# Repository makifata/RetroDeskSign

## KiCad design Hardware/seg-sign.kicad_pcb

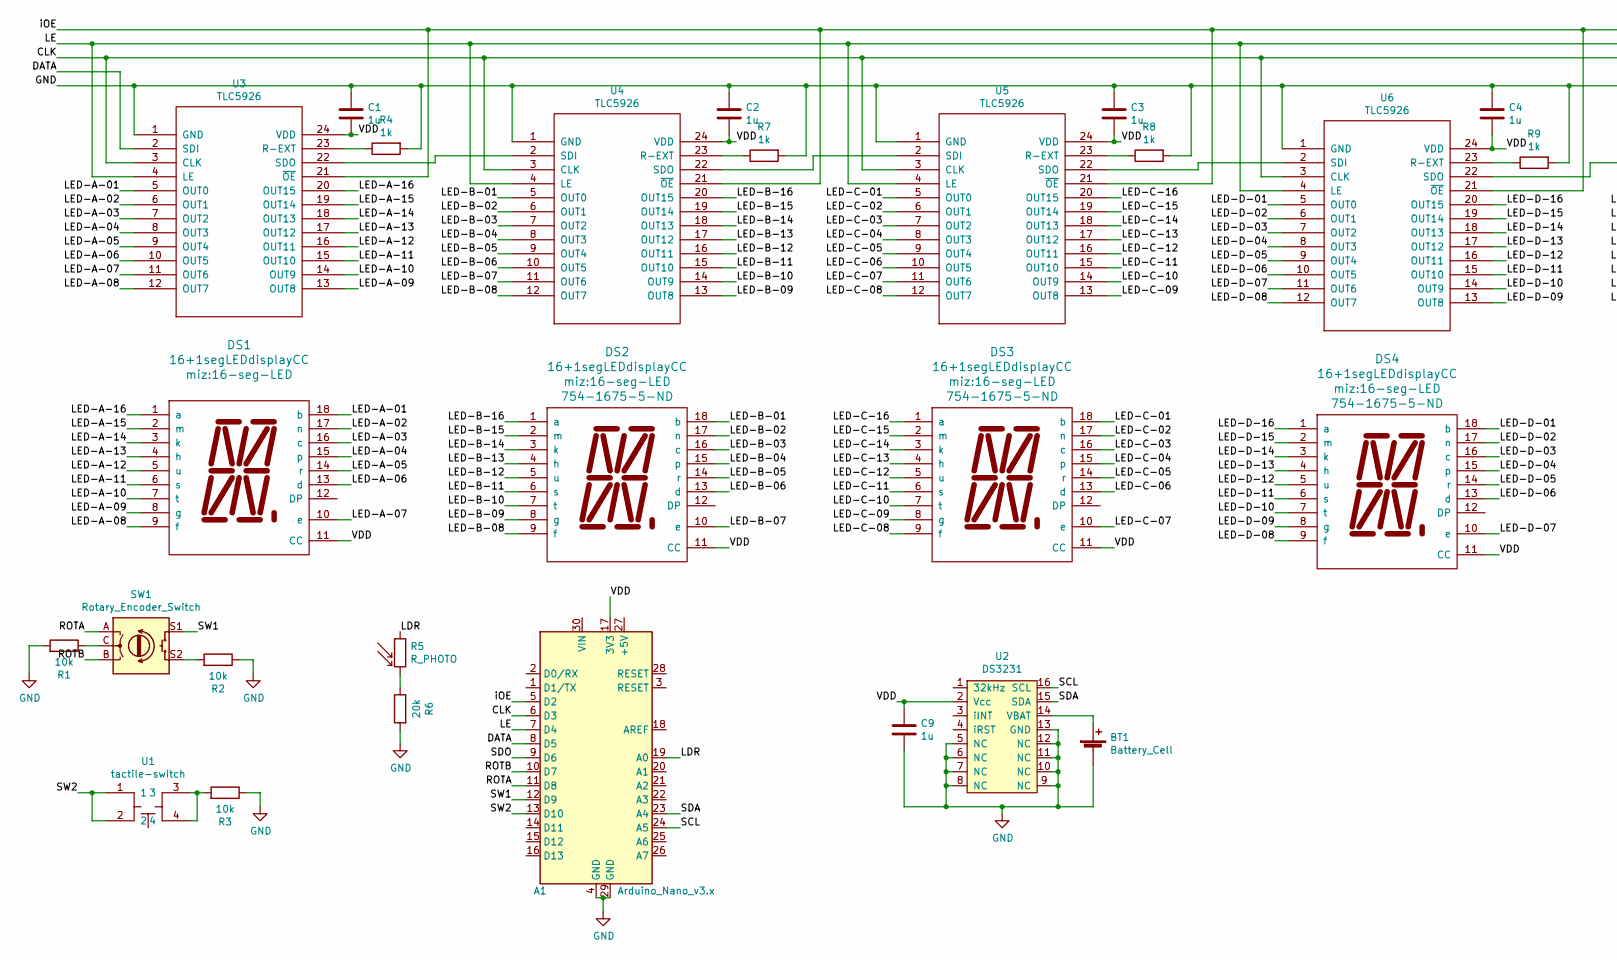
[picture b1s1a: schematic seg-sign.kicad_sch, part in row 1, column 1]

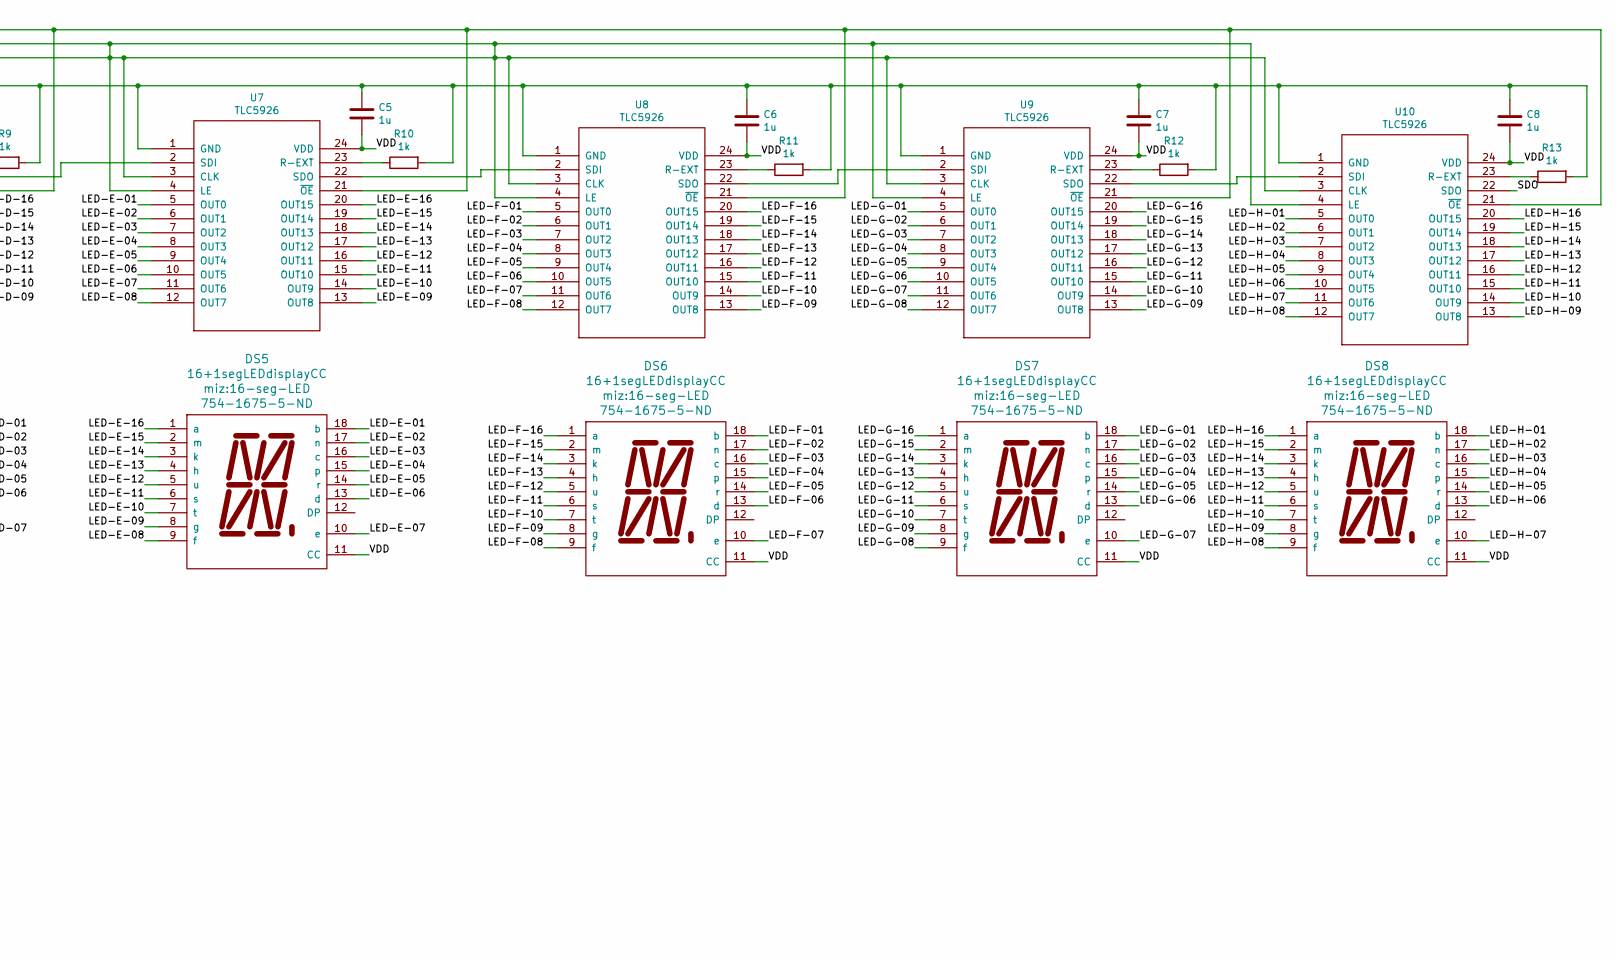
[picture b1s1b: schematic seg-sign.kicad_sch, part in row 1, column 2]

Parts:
A1: Arduino_Nano_v3.x; Arduino_Nano
BT1: Battery_Cell; CR1220-leystone; Digikey 36-2894-ND
C1, C2, C3, C4, C5, C6, C7, C8, C9: 1u; C_0603_1608Metric_Pad1.05x0.95mm_HandSolder
DS1, DS2: 16+1segLEDdisplayCC; 16-seg-LED; Digikey 754-1675-5-ND
DS3, DS4, DS5, DS6, DS7, DS8: 16+1segLEDdisplayCC; 16-seg-LED
R1, R2, R3: 10k; R_0603_1608Metric_Pad1.05x0.95mm_HandSolder
R4, R7, R8, R9, R10, R11, R12, R13: 1k; R_0603_1608Metric_Pad1.05x0.95mm_HandSolder
R5: R_PHOTO; R_LDR_5.0x4.1mm_P3mm_Vertical; Digikey PDV-P8104-ND
R6: 20k; R_0603_1608Metric_Pad1.05x0.95mm_HandSolder
SW1: Rotary_Encoder_Switch; PEC11R; Digikey PEC11R-4215F-S0012
U1: tactile-switch; Tactile-switch-450-1650-ND; Digikey 450-1650-ND
U2: DS3231; SOIC-16W_7.5x10.3mm_P1.27mm; Digikey DS3231S#T&RCT-ND
U3, U4, U5, U6, U7, U8, U9, U10: TLC5926; MODULE; Digikey 296-24760-1-ND

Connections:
/CLK: A1.6 (D3), A1.7 (D4), U3.3 (CLK), U3.4 (LE), U4.3 (CLK), U4.4 (LE), U5.3 (CLK), U5.4 (LE), U6.3 (CLK), U6.4 (LE), U7.3 (CLK), U7.4 (LE), U8.3 (CLK), U8.4 (LE), U9.3 (CLK), U9.4 (LE), U10.3 (CLK), U10.4 (LE)
/DATA: A1.8 (D5), U3.2 (SDI)
/LDR: A1.19 (A0), R5.1
/LED-A-01: DS1.18 (b), U3.5 (OUT0)
/LED-A-02: DS1.17 (n), U3.6 (OUT1)
/LED-A-03: DS1.16 (c), U3.7 (OUT2)
/LED-A-04: DS1.15 (p), U3.8 (OUT3)
/LED-A-05: DS1.14 (r), U3.9 (OUT4)
/LED-A-06: DS1.13 (d), U3.10 (OUT5)
/LED-A-07: DS1.10 (e), U3.11 (OUT6)
/LED-A-08: DS1.9 (f), U3.12 (OUT7)
/LED-A-09: DS1.8 (g), U3.13 (OUT8)
/LED-A-10: DS1.7 (t), U3.14 (OUT9)
/LED-A-11: DS1.6 (s), U3.15 (OUT10)
/LED-A-12: DS1.5 (u), U3.16 (OUT11)
/LED-A-13: DS1.4 (h), U3.17 (OUT12)
/LED-A-14: DS1.3 (k), U3.18 (OUT13)
/LED-A-15: DS1.2 (m), U3.19 (OUT14)
/LED-A-16: DS1.1 (a), U3.20 (OUT15)
/LED-B-01: DS2.18 (b), U4.5 (OUT0)
/LED-B-02: DS2.17 (n), U4.6 (OUT1)
/LED-B-03: DS2.16 (c), U4.7 (OUT2)
/LED-B-04: DS2.15 (p), U4.8 (OUT3)
/LED-B-05: DS2.14 (r), U4.9 (OUT4)
/LED-B-06: DS2.13 (d), U4.10 (OUT5)
/LED-B-07: DS2.10 (e), U4.11 (OUT6)
/LED-B-08: DS2.9 (f), U4.12 (OUT7)
/LED-B-09: DS2.8 (g), U4.13 (OUT8)
/LED-B-10: DS2.7 (t), U4.14 (OUT9)
/LED-B-11: DS2.6 (s), U4.15 (OUT10)
/LED-B-12: DS2.5 (u), U4.16 (OUT11)
/LED-B-13: DS2.4 (h), U4.17 (OUT12)
/LED-B-14: DS2.3 (k), U4.18 (OUT13)
/LED-B-15: DS2.2 (m), U4.19 (OUT14)
/LED-B-16: DS2.1 (a), U4.20 (OUT15)
/LED-C-01: DS3.18 (b), U5.5 (OUT0)
/LED-C-02: DS3.17 (n), U5.6 (OUT1)
/LED-C-03: DS3.16 (c), U5.7 (OUT2)
/LED-C-04: DS3.15 (p), U5.8 (OUT3)
/LED-C-05: DS3.14 (r), U5.9 (OUT4)
/LED-C-06: DS3.13 (d), U5.10 (OUT5)
/LED-C-07: DS3.10 (e), U5.11 (OUT6)
/LED-C-08: DS3.9 (f), U5.12 (OUT7)
/LED-C-09: DS3.8 (g), U5.13 (OUT8)
/LED-C-10: DS3.7 (t), U5.14 (OUT9)
/LED-C-11: DS3.6 (s), U5.15 (OUT10)
/LED-C-12: DS3.5 (u), U5.16 (OUT11)
/LED-C-13: DS3.4 (h), U5.17 (OUT12)
/LED-C-14: DS3.3 (k), U5.18 (OUT13)
/LED-C-15: DS3.2 (m), U5.19 (OUT14)
/LED-C-16: DS3.1 (a), U5.20 (OUT15)
/LED-D-01: DS4.18 (b), U6.5 (OUT0)
/LED-D-02: DS4.17 (n), U6.6 (OUT1)
/LED-D-03: DS4.16 (c), U6.7 (OUT2)
/LED-D-04: DS4.15 (p), U6.8 (OUT3)
/LED-D-05: DS4.14 (r), U6.9 (OUT4)
/LED-D-06: DS4.13 (d), U6.10 (OUT5)
/LED-D-07: DS4.10 (e), U6.11 (OUT6)
/LED-D-08: DS4.9 (f), U6.12 (OUT7)
/LED-D-09: DS4.8 (g), U6.13 (OUT8)
/LED-D-10: DS4.7 (t), U6.14 (OUT9)
/LED-D-11: DS4.6 (s), U6.15 (OUT10)
/LED-D-12: DS4.5 (u), U6.16 (OUT11)
/LED-D-13: DS4.4 (h), U6.17 (OUT12)
/LED-D-14: DS4.3 (k), U6.18 (OUT13)
/LED-D-15: DS4.2 (m), U6.19 (OUT14)
/LED-D-16: DS4.1 (a), U6.20 (OUT15)
/LED-E-01: DS5.18 (b), U7.5 (OUT0)
/LED-E-02: DS5.17 (n), U7.6 (OUT1)
/LED-E-03: DS5.16 (c), U7.7 (OUT2)
/LED-E-04: DS5.15 (p), U7.8 (OUT3)
/LED-E-05: DS5.14 (r), U7.9 (OUT4)
/LED-E-06: DS5.13 (d), U7.10 (OUT5)
/LED-E-07: DS5.10 (e), U7.11 (OUT6)
/LED-E-08: DS5.9 (f), U7.12 (OUT7)
/LED-E-09: DS5.8 (g), U7.13 (OUT8)
/LED-E-10: DS5.7 (t), U7.14 (OUT9)
/LED-E-11: DS5.6 (s), U7.15 (OUT10)
/LED-E-12: DS5.5 (u), U7.16 (OUT11)
/LED-E-13: DS5.4 (h), U7.17 (OUT12)
/LED-E-14: DS5.3 (k), U7.18 (OUT13)
/LED-E-15: DS5.2 (m), U7.19 (OUT14)
/LED-E-16: DS5.1 (a), U7.20 (OUT15)
/LED-F-01: DS6.18 (b), U8.5 (OUT0)
/LED-F-02: DS6.17 (n), U8.6 (OUT1)
/LED-F-03: DS6.16 (c), U8.7 (OUT2)
/LED-F-04: DS6.15 (p), U8.8 (OUT3)
/LED-F-05: DS6.14 (r), U8.9 (OUT4)
/LED-F-06: DS6.13 (d), U8.10 (OUT5)
/LED-F-07: DS6.10 (e), U8.11 (OUT6)
/LED-F-08: DS6.9 (f), U8.12 (OUT7)
/LED-F-09: DS6.8 (g), U8.13 (OUT8)
/LED-F-10: DS6.7 (t), U8.14 (OUT9)
/LED-F-11: DS6.6 (s), U8.15 (OUT10)
/LED-F-12: DS6.5 (u), U8.16 (OUT11)
/LED-F-13: DS6.4 (h), U8.17 (OUT12)
/LED-F-14: DS6.3 (k), U8.18 (OUT13)
/LED-F-15: DS6.2 (m), U8.19 (OUT14)
/LED-F-16: DS6.1 (a), U8.20 (OUT15)
/LED-G-01: DS7.18 (b), U9.5 (OUT0)
/LED-G-02: DS7.17 (n), U9.6 (OUT1)
/LED-G-03: DS7.16 (c), U9.7 (OUT2)
/LED-G-04: DS7.15 (p), U9.8 (OUT3)
/LED-G-05: DS7.14 (r), U9.9 (OUT4)
/LED-G-06: DS7.13 (d), U9.10 (OUT5)
/LED-G-07: DS7.10 (e), U9.11 (OUT6)
/LED-G-08: DS7.9 (f), U9.12 (OUT7)
/LED-G-09: DS7.8 (g), U9.13 (OUT8)
/LED-G-10: DS7.7 (t), U9.14 (OUT9)
/LED-G-11: DS7.6 (s), U9.15 (OUT10)
/LED-G-12: DS7.5 (u), U9.16 (OUT11)
/LED-G-13: DS7.4 (h), U9.17 (OUT12)
/LED-G-14: DS7.3 (k), U9.18 (OUT13)
/LED-G-15: DS7.2 (m), U9.19 (OUT14)
/LED-G-16: DS7.1 (a), U9.20 (OUT15)
/LED-H-01: DS8.18 (b), U10.5 (OUT0)
/LED-H-02: DS8.17 (n), U10.6 (OUT1)
/LED-H-03: DS8.16 (c), U10.7 (OUT2)
/LED-H-04: DS8.15 (p), U10.8 (OUT3)
/LED-H-05: DS8.14 (r), U10.9 (OUT4)
/LED-H-06: DS8.13 (d), U10.10 (OUT5)
/LED-H-07: DS8.10 (e), U10.11 (OUT6)
/LED-H-08: DS8.9 (f), U10.12 (OUT7)
/LED-H-09: DS8.8 (g), U10.13 (OUT8)
/LED-H-10: DS8.7 (t), U10.14 (OUT9)
/LED-H-11: DS8.6 (s), U10.15 (OUT10)
/LED-H-12: DS8.5 (u), U10.16 (OUT11)
/LED-H-13: DS8.4 (h), U10.17 (OUT12)
/LED-H-14: DS8.3 (k), U10.18 (OUT13)
/LED-H-15: DS8.2 (m), U10.19 (OUT14)
/LED-H-16: DS8.1 (a), U10.20 (OUT15)
/ROTA: A1.11 (D8), SW1.A
/ROTB: A1.10 (D7), SW1.B
/SCL: A1.24 (A5), U2.16 (SCL)
/SDA: A1.23 (A4), U2.15 (SDA)
/SDO: A1.9 (D6), U10.22 (SDO)
/SW1: A1.12 (D9), SW1.S1
/SW2: A1.13 (D10), U1.1, U1.2
/VDD: A1.17 (3V3), C1.2, C2.2, C3.2, C4.2, C5.2, C6.2, C7.2, C8.2, C9.1, DS1.11 (CC), DS2.11 (CC), DS3.11 (CC), DS4.11 (CC), DS5.11 (CC), DS6.11 (CC), DS7.11 (CC), DS8.11 (CC), U2.2 (Vcc), U3.24 (VDD), U4.24 (VDD), U5.24 (VDD), U6.24 (VDD), U7.24 (VDD), U8.24 (VDD), U9.24 (VDD), U10.24 (VDD)
/iOE: A1.5 (D2), U3.21 (~OE), U4.21 (~OE), U5.21 (~OE), U6.21 (~OE), U7.21 (~OE), U8.21 (~OE), U9.21 (~OE), U10.21 (~OE)
GND: A1.4 (GND), A1.29 (GND), BT1.2 (-), C1.1, C2.1, C3.1, C4.1, C5.1, C6.1, C7.1, C8.1, C9.2, R1.2, R2.1, R3.1, R4.2, R6.2, R7.2, R8.2, R9.2, R10.2, R11.2, R12.2, R13.2, U2.5 (NC), U2.6 (NC), U2.7 (NC), U2.8 (NC), U2.9 (NC), U2.10 (NC), U2.11 (NC), U2.12 (NC), U2.13 (GND), U3.1 (GND), U4.1 (GND), U5.1 (GND), U6.1 (GND), U7.1 (GND), U8.1 (GND), U9.1 (GND), U10.1 (GND)
unnamed: BT1.1 (+), U2.14 (VBAT)
unnamed: R1.1, SW1.C
unnamed: R2.2, SW1.S2
unnamed: R3.2, U1.3, U1.4
unnamed: R4.1, U3.23 (R-EXT)
unnamed: R5.2, R6.1
unnamed: R7.1, U4.23 (R-EXT)
unnamed: R8.1, U5.23 (R-EXT)
unnamed: R9.1, U6.23 (R-EXT)
unnamed: R10.1, U7.23 (R-EXT)
unnamed: R11.1, U8.23 (R-EXT)
unnamed: R12.1, U9.23 (R-EXT)
unnamed: R13.1, U10.23 (R-EXT)
unnamed: U3.22 (SDO), U4.2 (SDI)
unnamed: U4.22 (SDO), U5.2 (SDI)
unnamed: U5.22 (SDO), U6.2 (SDI)
unnamed: U6.22 (SDO), U7.2 (SDI)
unnamed: U7.22 (SDO), U8.2 (SDI)
unnamed: U8.22 (SDO), U9.2 (SDI)
unnamed: U9.22 (SDO), U10.2 (SDI)

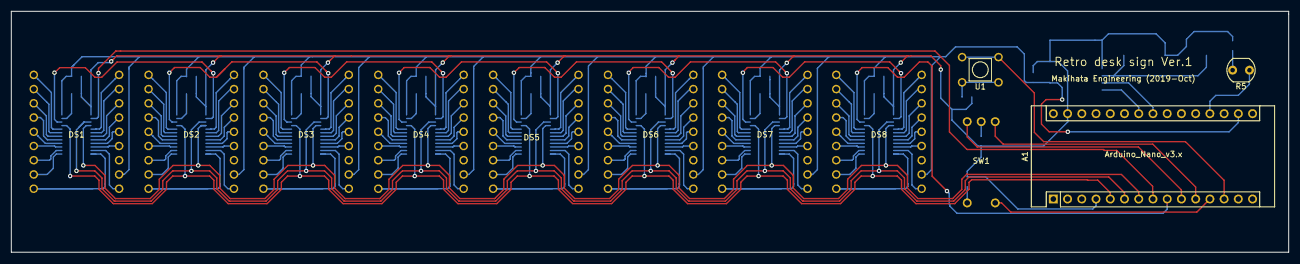
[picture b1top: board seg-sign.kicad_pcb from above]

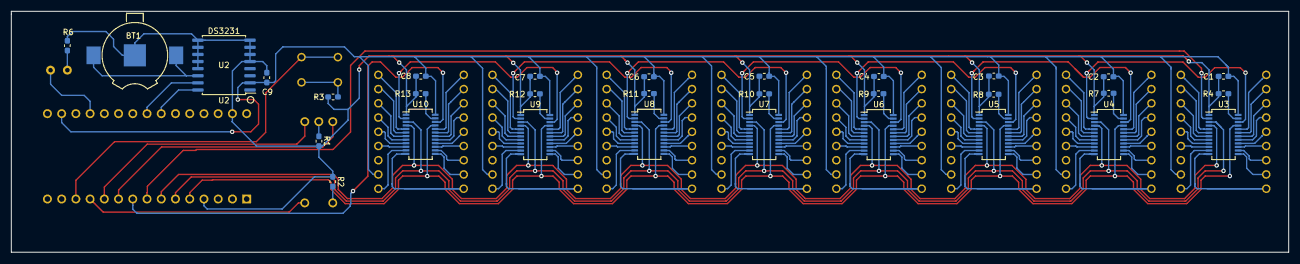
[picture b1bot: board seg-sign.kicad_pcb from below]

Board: 2 copper layers, 228.0 x 43.0 mm, 43 parts (31 on the bottom side), 161 nets.

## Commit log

2023-03-26 organize
